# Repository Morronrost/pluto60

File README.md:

# PLUTO60
The PLUTO60 is a 60% PCB designed for Space Invader switches. The MCU Board is the Xiao RP2040 from Seeed.

## Features
- Space Invader switches (Hitek 725)
- PRK Firmware
- Japanese Duplex Matrix
- USB C
- GH60 Compatible 
- Confirmed Working (Newest revision has not been tested, proceed at your own risk)
## Layout
Due to pin limitations, the PLUTO60 has a fixed ISO layout without split left-shift. It can however be used in an winkeyless configuration if desired.

## Instructions

1. Install PRK and place the keymap on the MCU
2. Solder all the switches in place
3. Clip the legs of the "Esc" and "1" switches that are under the MCU
4. Solder the MCU

# Custom keymap

Instructions on how to make a custom keymap can be found on the [PRK Firmware wiki](https://github.com/picoruby/prk_firmware/wiki/).

## Credits
- Engicoder & Gvalch'ca for the Hitek 725 footprints
- amtra5 & _spindle for GH60 template footprints
- Inozenz for bringing Space Invaders to the masses
- Hasumikin for PRK Firmware
- Seeed for the free PCBs

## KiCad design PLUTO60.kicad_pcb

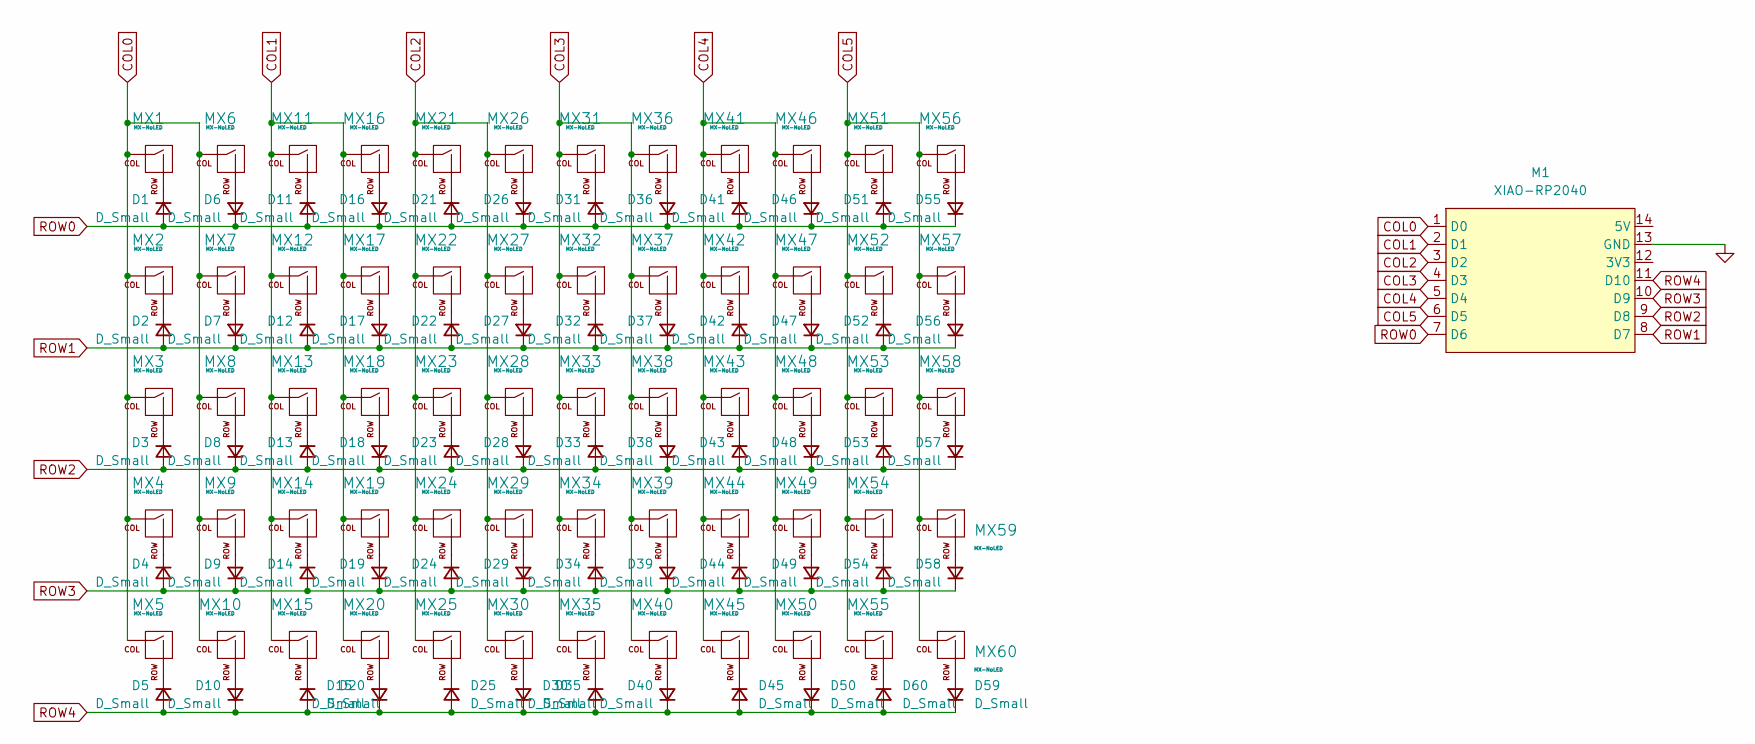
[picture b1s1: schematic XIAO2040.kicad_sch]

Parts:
D1, D2, D3, D4, D5, D6, D7, D8, D9, D10, D11, D12, D13, D14, D15, D16, D17, D18, D19, D20, D21, D22, D23, D24, D25, D26, D27, D28, D29, D30, D31, D32, D33, D34, D35, D36, D37, D38, D39, D40, D41, D42, D43, D44, D45, D46, D47, D48, D49, D50, D51, D52, D53, D54, D55, D56, D57, D58, D59, D60: D_Small; D_SOD-123
M1: XIAO-RP2040
MX1, MX6, MX7, MX8, MX9, MX10, MX11, MX12, MX13, MX14, MX16, MX17, MX18, MX19, MX21, MX22, MX23, MX24, MX26, MX27, MX28, MX29, MX30, MX31, MX32, MX33, MX34, MX36, MX37, MX38, MX39, MX40, MX41, MX42, MX43, MX44, MX46, MX47, MX48, MX49, MX51, MX52, MX53, MX54, MX55, MX56, MX57, MX58, MX60: MX-NoLED; Hitek725-1U
MX2, MX5, MX15, MX25, MX35: MX-NoLED; Hitek725-1.5U
MX3: MX-NoLED; Hitek725-1.75U
MX4: MX-NoLED; Hitek725-2.25U
MX20: MX-NoLED; Hitek725-7U
MX45: MX-NoLED; Hitek725-2U
MX50: MX-NoLED; Hitek725-BigAssEnter-separated-pins
MX59: MX-NoLED; Hitek725-2.75U

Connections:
COL0: M1.1 (D0), MX1.1 (COL), MX2.1 (COL), MX3.1 (COL), MX4.1 (COL), MX5.1 (COL), MX6.1 (COL), MX7.1 (COL), MX8.1 (COL), MX9.1 (COL), MX10.1 (COL)
COL1: M1.2 (D1), MX11.1 (COL), MX12.1 (COL), MX13.1 (COL), MX14.1 (COL), MX15.1 (COL), MX16.1 (COL), MX17.1 (COL), MX18.1 (COL), MX19.1 (COL), MX20.1 (COL)
COL2: M1.3 (D2), MX21.1 (COL), MX22.1 (COL), MX23.1 (COL), MX24.1 (COL), MX25.1 (COL), MX26.1 (COL), MX27.1 (COL), MX28.1 (COL), MX29.1 (COL), MX30.1 (COL)
COL3: M1.4 (D3), MX31.1 (COL), MX32.1 (COL), MX33.1 (COL), MX34.1 (COL), MX35.1 (COL), MX36.1 (COL), MX37.1 (COL), MX38.1 (COL), MX39.1 (COL), MX40.1 (COL)
COL4: M1.5 (D4), MX41.1 (COL), MX42.1 (COL), MX43.1 (COL), MX44.1 (COL), MX45.1 (COL), MX46.1 (COL), MX47.1 (COL), MX48.1 (COL), MX49.1 (COL), MX50.1 (COL)
COL5: M1.6 (D5), MX51.1 (COL), MX52.1 (COL), MX53.1 (COL), MX54.1 (COL), MX55.1 (COL), MX56.1 (COL), MX57.1 (COL), MX58.1 (COL), MX59.1 (COL), MX60.1 (COL)
GND: M1.13 (GND)
unnamed: D1.1 (K), MX1.2 (ROW)
unnamed: D2.1 (K), MX2.2 (ROW)
unnamed: D3.1 (K), MX3.2 (ROW)
unnamed: D4.1 (K), MX4.2 (ROW)
unnamed: D5.1 (K), MX5.2 (ROW)
unnamed: D6.2 (A), MX6.2 (ROW)
unnamed: D7.2 (A), MX7.2 (ROW)
unnamed: D8.2 (A), MX8.2 (ROW)
unnamed: D9.2 (A), MX9.2 (ROW)
unnamed: D10.2 (A), MX10.2 (ROW)
unnamed: D11.1 (K), MX11.2 (ROW)
unnamed: D12.1 (K), MX12.2 (ROW)
unnamed: D13.1 (K), MX13.2 (ROW)
unnamed: D14.1 (K), MX14.2 (ROW)
unnamed: D15.1 (K), MX15.2 (ROW)
unnamed: D16.2 (A), MX16.2 (ROW)
unnamed: D17.2 (A), MX17.2 (ROW)
unnamed: D18.2 (A), MX18.2 (ROW)
unnamed: D19.2 (A), MX19.2 (ROW)
unnamed: D20.2 (A), MX20.2 (ROW)
unnamed: D21.1 (K), MX21.2 (ROW)
unnamed: D22.1 (K), MX22.2 (ROW)
unnamed: D23.1 (K), MX23.2 (ROW)
unnamed: D24.1 (K), MX24.2 (ROW)
unnamed: D25.1 (K), MX25.2 (ROW)
unnamed: D26.2 (A), MX26.2 (ROW)
unnamed: D27.2 (A), MX27.2 (ROW)
unnamed: D28.2 (A), MX28.2 (ROW)
unnamed: D29.2 (A), MX29.2 (ROW)
unnamed: D30.2 (A), MX30.2 (ROW)
unnamed: D31.1 (K), MX31.2 (ROW)
unnamed: D32.1 (K), MX32.2 (ROW)
unnamed: D33.1 (K), MX33.2 (ROW)
unnamed: D34.1 (K), MX34.2 (ROW)
unnamed: D35.1 (K), MX35.2 (ROW)
unnamed: D36.2 (A), MX36.2 (ROW)
unnamed: D37.2 (A), MX37.2 (ROW)
unnamed: D38.2 (A), MX38.2 (ROW)
unnamed: D39.2 (A), MX39.2 (ROW)
unnamed: D40.2 (A), MX40.2 (ROW)
unnamed: D41.1 (K), MX41.2 (ROW)
unnamed: D42.1 (K), MX42.2 (ROW)
unnamed: D43.1 (K), MX43.2 (ROW)
unnamed: D44.1 (K), MX44.2 (ROW)
unnamed: D45.1 (K), MX45.2 (ROW)
unnamed: D46.2 (A), MX46.2 (ROW)
unnamed: D47.2 (A), MX47.2 (ROW)
unnamed: D48.2 (A), MX48.2 (ROW)
unnamed: D49.2 (A), MX49.2 (ROW)
unnamed: D50.2 (A), MX50.2 (ROW)
unnamed: D51.1 (K), MX51.2 (ROW)
unnamed: D52.1 (K), MX52.2 (ROW)
unnamed: D53.1 (K), MX53.2 (ROW)
unnamed: D54.1 (K), MX54.2 (ROW)
unnamed: D55.2 (A), MX56.2 (ROW)
unnamed: D56.2 (A), MX57.2 (ROW)
unnamed: D57.2 (A), MX58.2 (ROW)
unnamed: D58.2 (A), MX59.2 (ROW)
unnamed: D59.2 (A), MX60.2 (ROW)
unnamed: D60.1 (K), MX55.2 (ROW)
ROW0: D1.2 (A), D6.1 (K), D11.2 (A), D16.1 (K), D21.2 (A), D26.1 (K), D31.2 (A), D36.1 (K), D41.2 (A), D46.1 (K), D51.2 (A), D55.1 (K), M1.7 (D6)
ROW1: D2.2 (A), D7.1 (K), D12.2 (A), D17.1 (K), D22.2 (A), D27.1 (K), D32.2 (A), D37.1 (K), D42.2 (A), D47.1 (K), D52.2 (A), D56.1 (K), M1.8 (D7)
ROW2: D3.2 (A), D8.1 (K), D13.2 (A), D18.1 (K), D23.2 (A), D28.1 (K), D33.2 (A), D38.1 (K), D43.2 (A), D48.1 (K), D53.2 (A), D57.1 (K), M1.9 (D8)
ROW3: D4.2 (A), D9.1 (K), D14.2 (A), D19.1 (K), D24.2 (A), D29.1 (K), D34.2 (A), D39.1 (K), D44.2 (A), D49.1 (K), D54.2 (A), D58.1 (K), M1.10 (D9)
ROW4: D5.2 (A), D10.1 (K), D15.2 (A), D20.1 (K), D25.2 (A), D30.1 (K), D35.2 (A), D40.1 (K), D45.2 (A), D50.1 (K), D59.1 (K), D60.2 (A), M1.11 (D10)

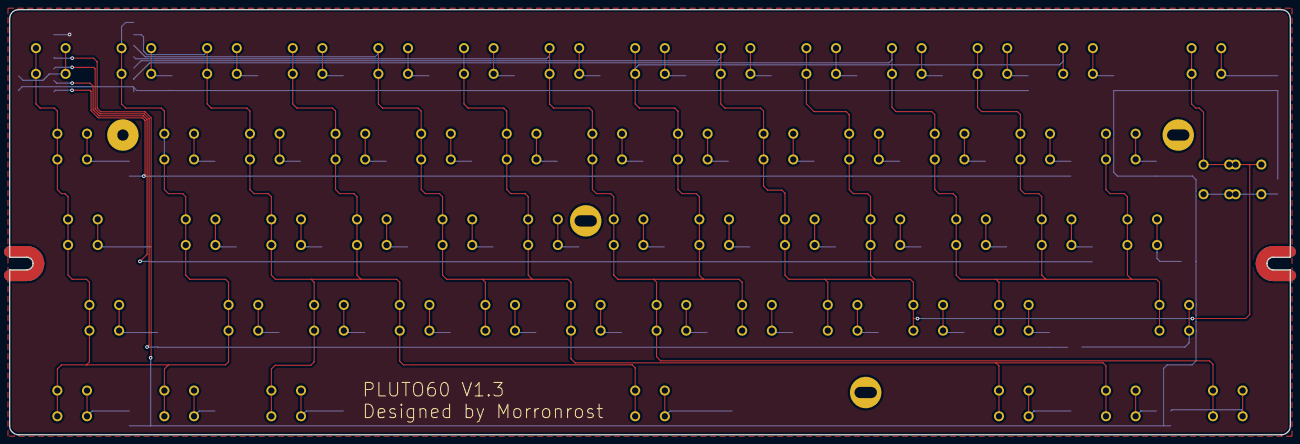
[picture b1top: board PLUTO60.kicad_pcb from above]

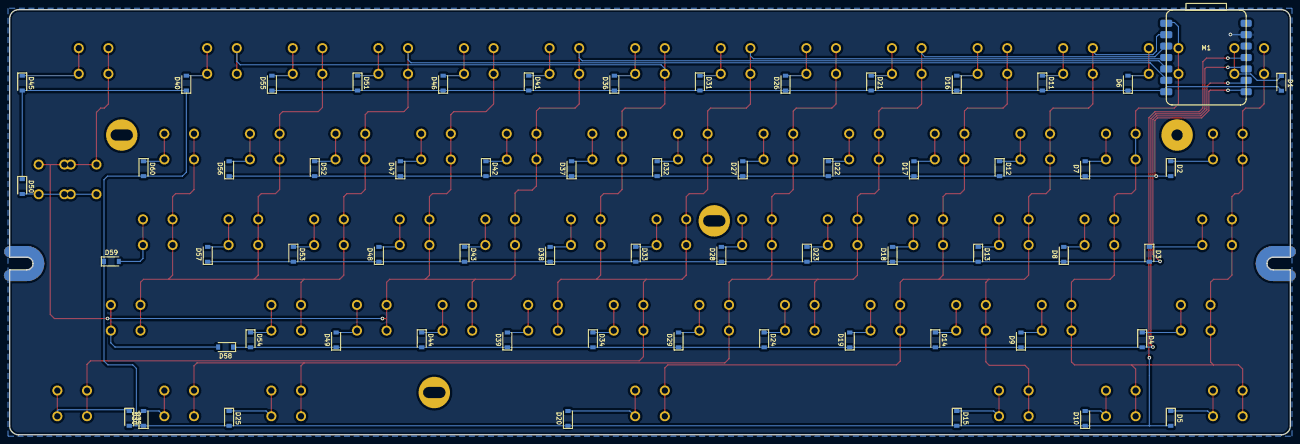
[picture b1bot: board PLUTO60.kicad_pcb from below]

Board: 2 copper layers, 285.0 x 94.6 mm, 121 parts (61 on the bottom side), 71 nets.

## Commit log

2022-07-07 Cleaned up repository
2022-07-07 Put files at repository root
2022-07-07 Added layout img
2022-08-29 Corrected MCU placement & tidied routing
